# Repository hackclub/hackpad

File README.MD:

Talk to @Ace (Zohair shaik) on slack Gmail: Zohairshaik7@gmail.com Discord: autohackingcodes2079Hi this is my hackpad submission:

________________________________________________
Why I made it:

Was pretty bored and saw some macropads on insta so i got inspired..
________________________________________________
What I need:

7x Cherry MX switches
2x SK6812 MINI Leds
7x Blank DSA Keycaps
________________________________________________

______________________________________________
Firmware used:

KMK

_______________________________________________

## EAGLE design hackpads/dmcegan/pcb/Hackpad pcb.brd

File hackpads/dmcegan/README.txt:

BOM:
1x PCB
1x RP2040
11x Cherry Mx switches (Milky Yellow)
11x Keycaps

What was your inspiration to make it?:
My inspiration was the fact that I had been looking at macropads for a while but never actually got around to making one. I also needed something to control the controls in certain apps like discord, fusion 360 and prusaslicer without resorting to complicated shortcuts.
Hardest challenges faced:
FIRMWARE. The firmware was the most complicated part of the build by far as ive designed pcbs and 3d models before. The firmware is still a bit iffy as all the guides I could find required the rp2040 to actually compile the full .uf2 fgile, so hopefully this is something to work on once i've to the physical parts.
Other fun facts to know:
This is something i've wanted to do for a while and now I get do do it! I think hack club is a great thing for high schoolers as it gives the motivation and funds to experiment and have fun with cool projects like this, so thanks guys!

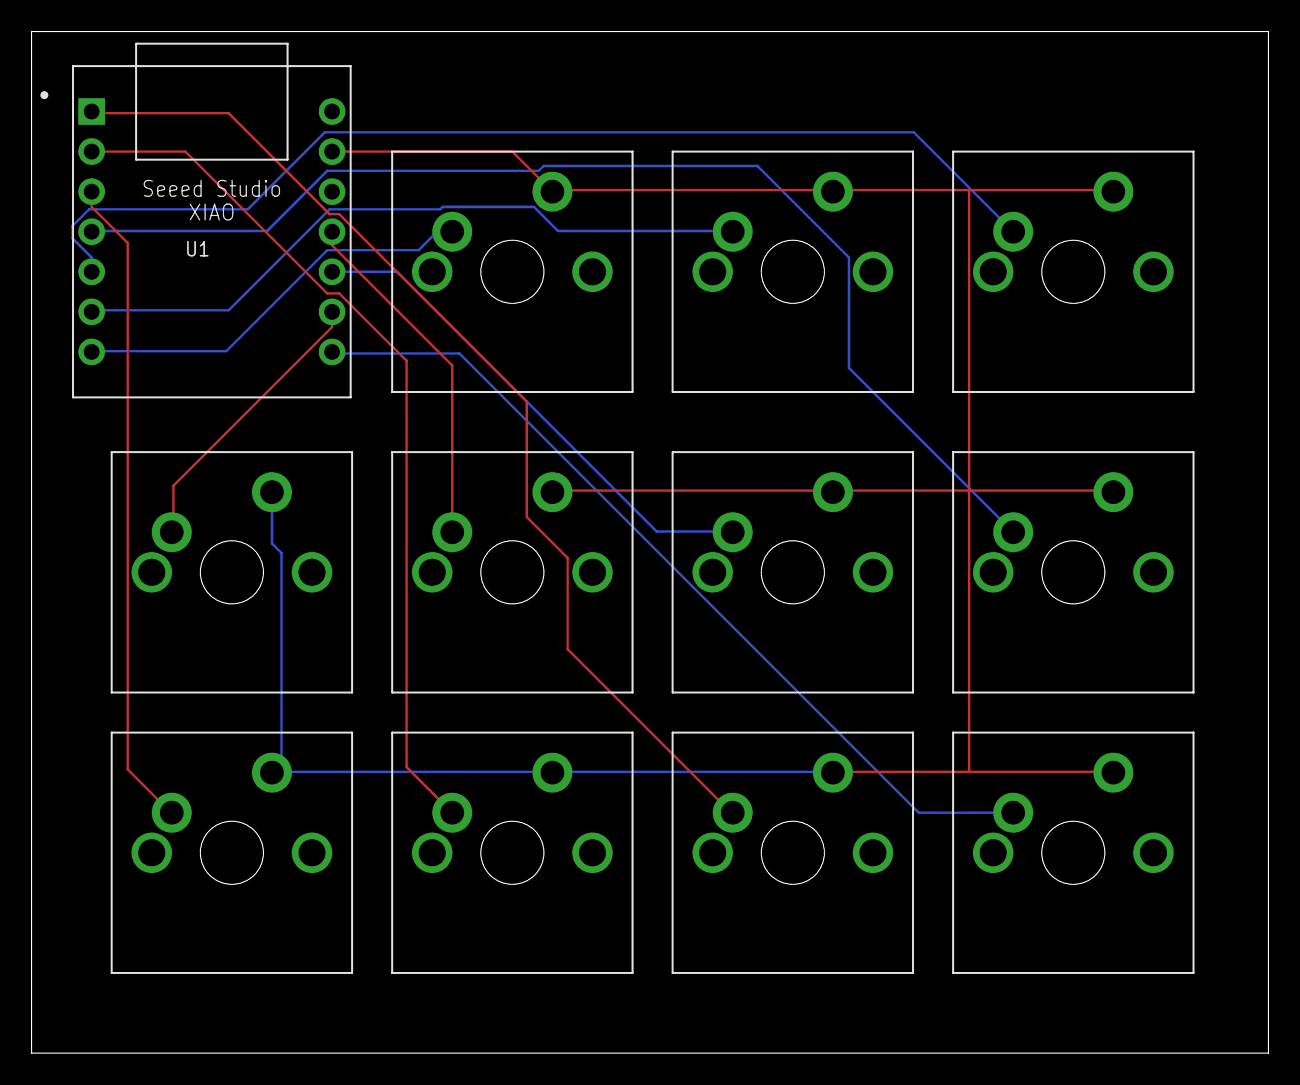
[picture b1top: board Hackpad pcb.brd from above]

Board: 2 copper layers, 78.4 x 64.8 mm, 12 parts (0 on the bottom side), 12 nets.

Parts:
U1: XIAO-THRUHOLE; XIAO-GENERIC-THRUHOLE-MODULE14P-2.54-21X17.8MM
U$1, U$2, U$3, U$4, U$5, U$6, U$7, U$8, U$9, U$10, U$11: CHERRY-MX

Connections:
GND: U1.13, U$1.SW2, U$2.SW2, U$3.SW2, U$4.SW2, U$5.SW2, U$6.SW2, U$7.SW2, U$8.SW2, U$9.SW2, U$10.SW2, U$11.SW2
unnamed: U1.1, U$5.SW1
unnamed: U1.2, U$6.SW1
unnamed: U1.3, U$7.SW1
unnamed: U1.4, U$8.SW1
unnamed: U1.5, U$9.SW1
unnamed: U1.6, U$10.SW1
unnamed: U1.7, U$11.SW1
unnamed: U1.11, U$1.SW1
unnamed: U1.10, U$2.SW1
unnamed: U1.9, U$3.SW1
unnamed: U1.8, U$4.SW1

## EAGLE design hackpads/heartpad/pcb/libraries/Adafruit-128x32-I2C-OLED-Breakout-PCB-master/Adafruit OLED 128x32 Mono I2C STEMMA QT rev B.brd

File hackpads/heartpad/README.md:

# Heartpad

## Firmware
**Things to Test:**

1. Please make sure that the display is working and is showing this image:
<!-- [oled display image](./Firmware/catswhite.bmp) -->

2. Please test the toggle key to toggle between layers

3. Please test the function keys on the first layer. You don't need to test the second layer, since I will use an application to create custom keybinds for those

## CAD 

- Please ensure that the case fits

## PCB

- It would be nice if you could double check my wiring on the PCB and schematic

## BOM

- 10x Cherry MX Switches

- 1x PCB - Color: Purple

- 1x 0.91" 128x32 I2C OLED Display

- 10x Through-hold 1N4148 Diodes

- Screws (18mm tall, 3mm diameter) with nuts

- 1x Case - Filament Color: Carmine Red Glitter Filament

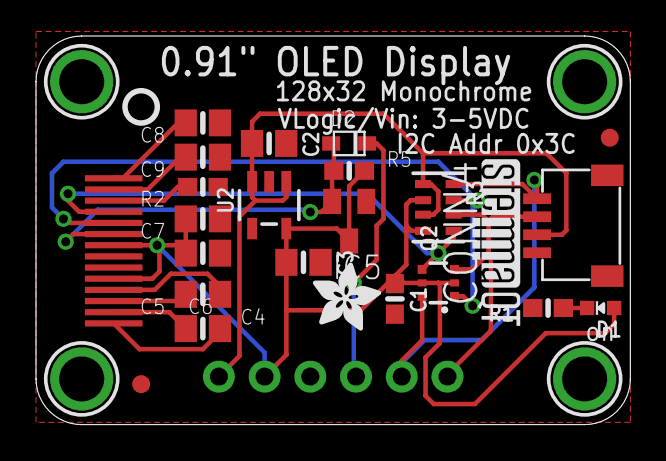
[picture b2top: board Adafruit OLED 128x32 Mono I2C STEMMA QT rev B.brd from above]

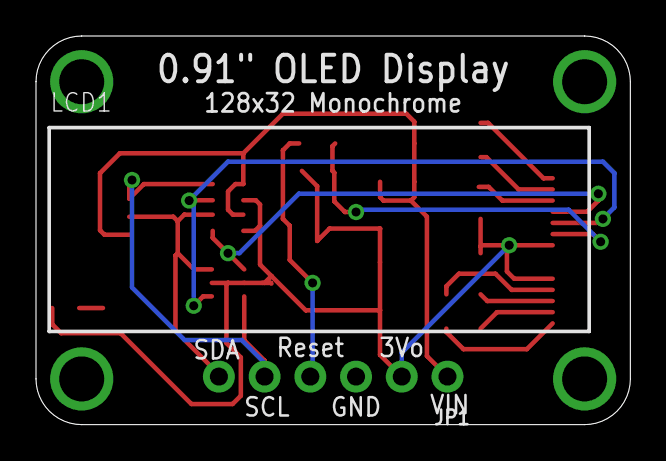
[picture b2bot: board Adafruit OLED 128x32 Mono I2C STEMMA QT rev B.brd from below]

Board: 2 copper layers, 33.0 x 21.6 mm, 30 parts (2 on the bottom side), 17 nets.

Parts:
C1: 0.1uF; 0603-NO
C2, C3, C8, C9: 10uF; 0805-NO
C4, C5, C6, C7: 1uF; 0805-NO
CONN4: STEMMA_I2C_QT; JST_SH4
D1: GREEN; CHIPLED_0603_NOOUTLINE
D2: 1N4148; SOD-323F
FID3, FID4: FIDUCIAL_1MM
IC5: APX803; SOT23
JP1: 1X06_ROUND_70
LCD1: UG-2832HSWEG02_WRAPUNDER
Q2: BSS138; SOT363
R1, R5: 10K; 0603-NO
R2: 390K; 0603-NO
R3: 10K; RESPACK_4X0603
U2: AP2112K-3.3; SOT23-5
U$1, U$17, U$19, U$21: MOUNTINGHOLE2.5; MOUNTINGHOLE_2.5_PLATED
U$22: ADAFRUIT_3.5MM
U$25: PCBFEAT-REV-040
U$31: STEMMAQT

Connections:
3.3V: C1.1, C3.1, C6.2, C7.2, D1.A, IC5.3, JP1.2, LCD1.5, LCD1.8, Q2.2, Q2.5, R3.2, R3.4, R5.2, U2.5
GND: C1.2, C2.2, C3.2, C6.1, C7.1, C8.1, C9.1, CONN4.1, IC5.1, JP1.3, LCD1.7, R1.2, R2.1, U2.2
unnamed: C4.2, LCD1.1
unnamed: D1.C, R1.1
unnamed: C4.1, LCD1.2
unnamed: C5.2, LCD1.3
unnamed: C5.1, LCD1.4
unnamed: C9.2, LCD1.13
unnamed: LCD1.12, R2.2
unnamed: C8.2, LCD1.14
RESET: D2.C, JP1.4
RES_3V: D2.A, IC5.2, LCD1.9, R5.1
SCL: CONN4.4, JP1.5, Q2.6, R3.8
SCL_3V: LCD1.10, Q2.1, R3.7
SDA: CONN4.3, JP1.6, Q2.3, R3.6
SDA_3V: LCD1.11, Q2.4, R3.5
VCC: C2.1, CONN4.2, JP1.1, R3.1, R3.3, U2.1, U2.3

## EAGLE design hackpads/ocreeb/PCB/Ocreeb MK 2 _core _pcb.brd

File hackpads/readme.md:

# madpad

* Keyboard Maintainer: [Meghana Madiraju](https://github.com/MeghanaM4)
* Hardware Supported: *The PCBs, controllers supported*
* Hardware Availability: *Links to where you can find this hardware*

Make example for this keyboard (after setting up your build environment):

    make madpad:default

Flashing example for this keyboard:

    make madpad:default:flash

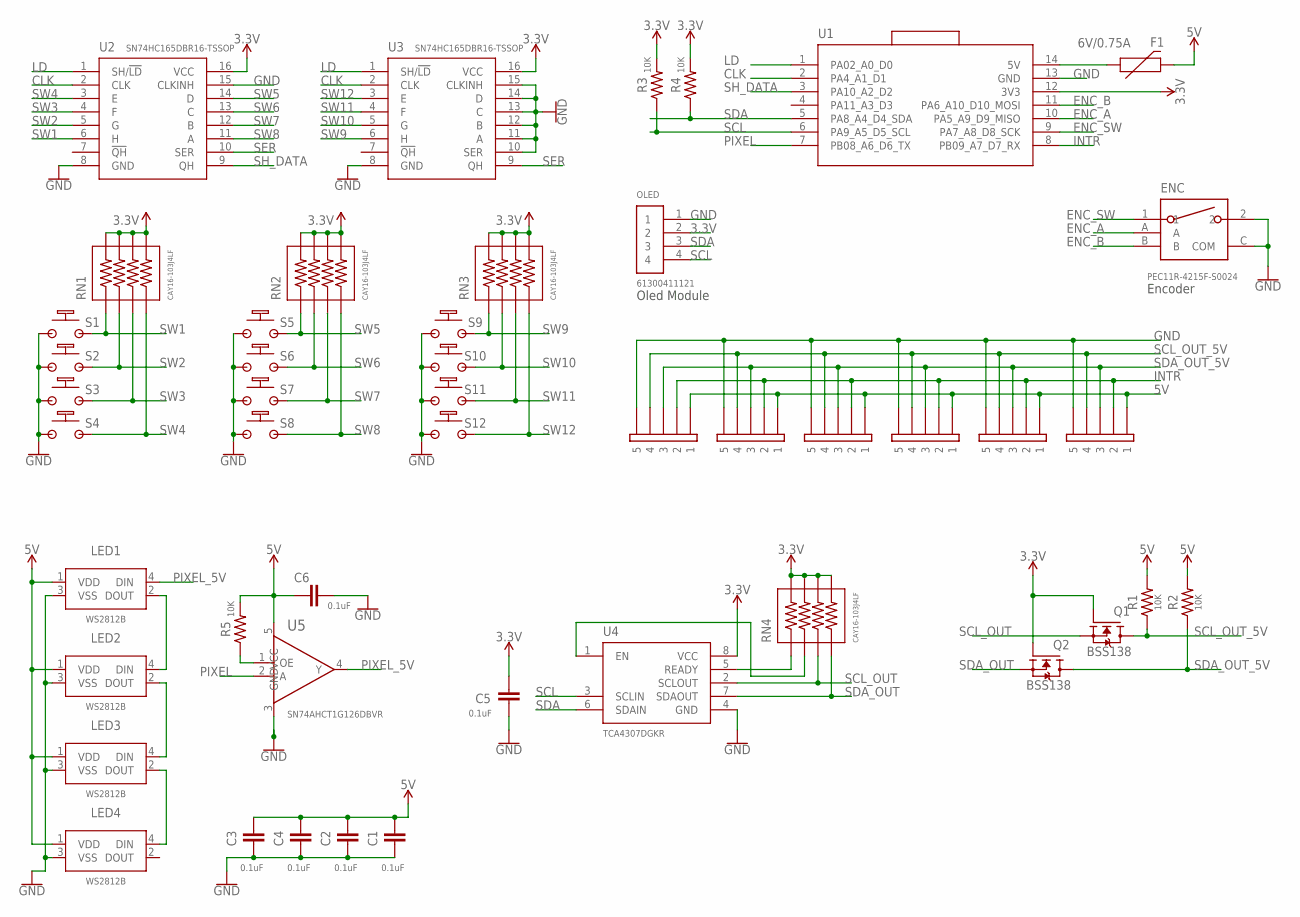
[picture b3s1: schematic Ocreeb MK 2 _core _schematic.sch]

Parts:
C1, C2, C3, C4, C5, C6: 0.1uF; CAPC1608X85
ENC: PEC11R-4215F-S0024
F1: 6V/0.75A; 1206
LED1, LED2, LED3, LED4: WS2812B
OLED: 61300411121
Q1, Q2: BSS138; SOT95P240X111-3N
R1, R2, R3, R4, R5: 10K; RESC1608X60
RN1, RN2, RN3, RN4: CAY16-103J4LF; RESCAF80P320X160X60-8N
S1, S2, S3, S4, S5, S6, S7, S8, S9, S10, S11, S12: MX1A-11NN; CHERRY_MX1A-11NN_SWITCH
U1: MOUDLE-SEEEDUINO-XIAO-SMD; MOUDLE14P-SMD-2.54-21X17.8MM
U2, U3: SN74HC165DBR16-TSSOP; SOP65P640X120-16N
U4: TCA4307DGKR; SOP65P490X110-8N
U5: SN74AHCT1G126DBVR; SOT95P280X145-5N
U$1, U$2, U$3, U$4, U$5, U$6: 5PIN_EDGE; 5_POGO_EDGE

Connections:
3.3V: C5.2, OLED.2, Q1.1 (G), Q2.1 (G), R3.2, R4.2, RN1.5, RN1.6, RN1.7, RN1.8, RN2.5, RN2.6, RN2.7, RN2.8, RN3.5, RN3.6, RN3.7, RN3.8, RN4.5, RN4.6, RN4.7, RN4.8, U1.12 (3V3), U2.16 (VCC), U3.16 (VCC), U4.8 (VCC)
5V: C1.2, C2.2, C3.2, C4.2, C6.2, F1.2, LED1.1 (VDD), LED2.1 (VDD), LED3.1 (VDD), LED4.1 (VDD), R1.2, R2.2, R5.2, U5.5 (VCC), U$1.1, U$2.1, U$3.1, U$4.1, U$5.1, U$6.1
CLK: U1.2 (PA4_A1_D1), U2.2 (CLK), U3.2 (CLK)
ENC_A: ENC.A, U1.10 (PA5_A9_D9_MISO)
ENC_B: ENC.B, U1.11 (PA6_A10_D10_MOSI)
ENC_SW: ENC.1, U1.9 (PA7_A8_D8_SCK)
GND: C1.1, C2.1, C3.1, C4.1, C5.1, C6.1, ENC.2, ENC.C (COM), LED1.3 (VSS), LED2.3 (VSS), LED3.3 (VSS), LED4.3 (VSS), OLED.1, S1.1, S1.1_ALT (1), S2.1, S2.1_ALT (1), S3.1, S3.1_ALT (1), S4.1, S4.1_ALT (1), S5.1, S5.1_ALT (1), S6.1, S6.1_ALT (1), S7.1, S7.1_ALT (1), S8.1, S8.1_ALT (1), S9.1, S9.1_ALT (1), S10.1, S10.1_ALT (1), S11.1, S11.1_ALT (1), S12.1, S12.1_ALT (1), U1.13 (GND), U2.8 (GND), U2.15 (CLKINH), U3.8 (GND), U3.10 (SER), U3.11 (A), U3.12 (B), U3.13 (C), U3.14 (D), U3.15 (CLKINH), U4.4 (GND), U5.3 (GND), U$1.5, U$2.5, U$3.5, U$4.5, U$5.5, U$6.5
INTR: U1.8 (PB09_A7_D7_RX), U$1.2, U$2.2, U$3.2, U$4.2, U$5.2, U$6.2
LD: U1.1 (PA02_A0_D0), U2.1 (SH/!LD), U3.1 (SH/!LD)
unnamed: RN4.1, U4.5 (READY)
unnamed: R5.1, U5.1 (OE)
unnamed: LED1.2 (DOUT), LED2.4 (DIN)
unnamed: LED2.2 (DOUT), LED3.4 (DIN)
unnamed: LED3.2 (DOUT), LED4.4 (DIN)
unnamed: RN4.2, U4.1 (EN)
PIXEL: U1.7 (PB08_A6_D6_TX), U5.2 (A)
PIXEL_5V: LED1.4 (DIN), U5.4 (Y)
SCL: OLED.4, R3.1, U1.6 (PA9_A5_D5_SCL), U4.3 (SCLIN)
SCL_OUT: Q1.2 (S), RN4.3, U4.2 (SCLOUT)
SCL_OUT_5V: Q1.3 (D), R1.1, U$1.4, U$2.4, U$3.4, U$4.4, U$5.4, U$6.4
SDA: OLED.3, R4.1, U1.5 (PA8_A4_D4_SDA), U4.6 (SDAIN)
SDA_OUT: Q2.2 (S), RN4.4, U4.7 (SDAOUT)
SDA_OUT_5V: Q2.3 (D), R2.1, U$1.3, U$2.3, U$3.3, U$4.3, U$5.3, U$6.3
SER: U2.10 (SER), U3.9 (QH)
SH_DATA: U1.3 (PA10_A2_D2), U2.9 (QH)
SW1: RN1.1, S1.2, S1.2_ALT (2), U2.6 (H)
SW2: RN1.2, S2.2, S2.2_ALT (2), U2.5 (G)
SW3: RN1.3, S3.2, S3.2_ALT (2), U2.4 (F)
SW4: RN1.4, S4.2, S4.2_ALT (2), U2.3 (E)
SW5: RN2.1, S5.2, S5.2_ALT (2), U2.14 (D)
SW6: RN2.2, S6.2, S6.2_ALT (2), U2.13 (C)
SW7: RN2.3, S7.2, S7.2_ALT (2), U2.12 (B)
SW8: RN2.4, S8.2, S8.2_ALT (2), U2.11 (A)
SW9: RN3.1, S9.2, S9.2_ALT (2), U3.6 (H)
SW10: RN3.2, S10.2, S10.2_ALT (2), U3.5 (G)
SW11: RN3.3, S11.2, S11.2_ALT (2), U3.4 (F)
SW12: RN3.4, S12.2, S12.2_ALT (2), U3.3 (E)
USB_5V: F1.1, U1.14 (5V)

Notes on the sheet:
Oled Module
Encoder

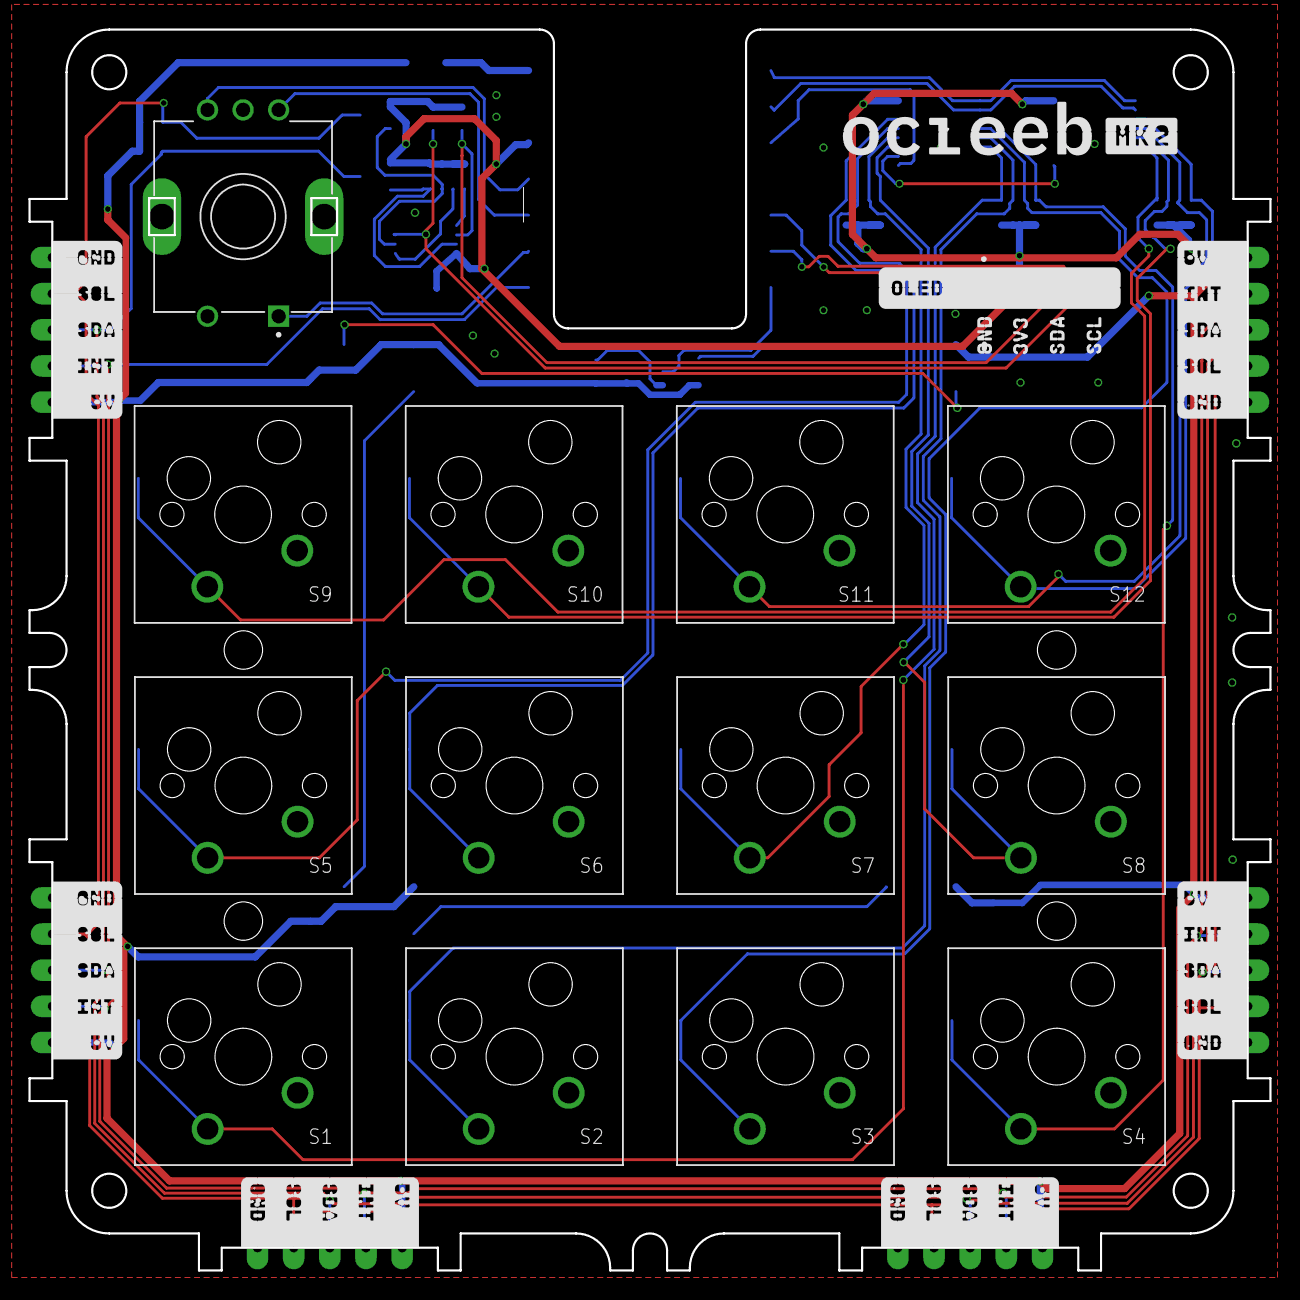
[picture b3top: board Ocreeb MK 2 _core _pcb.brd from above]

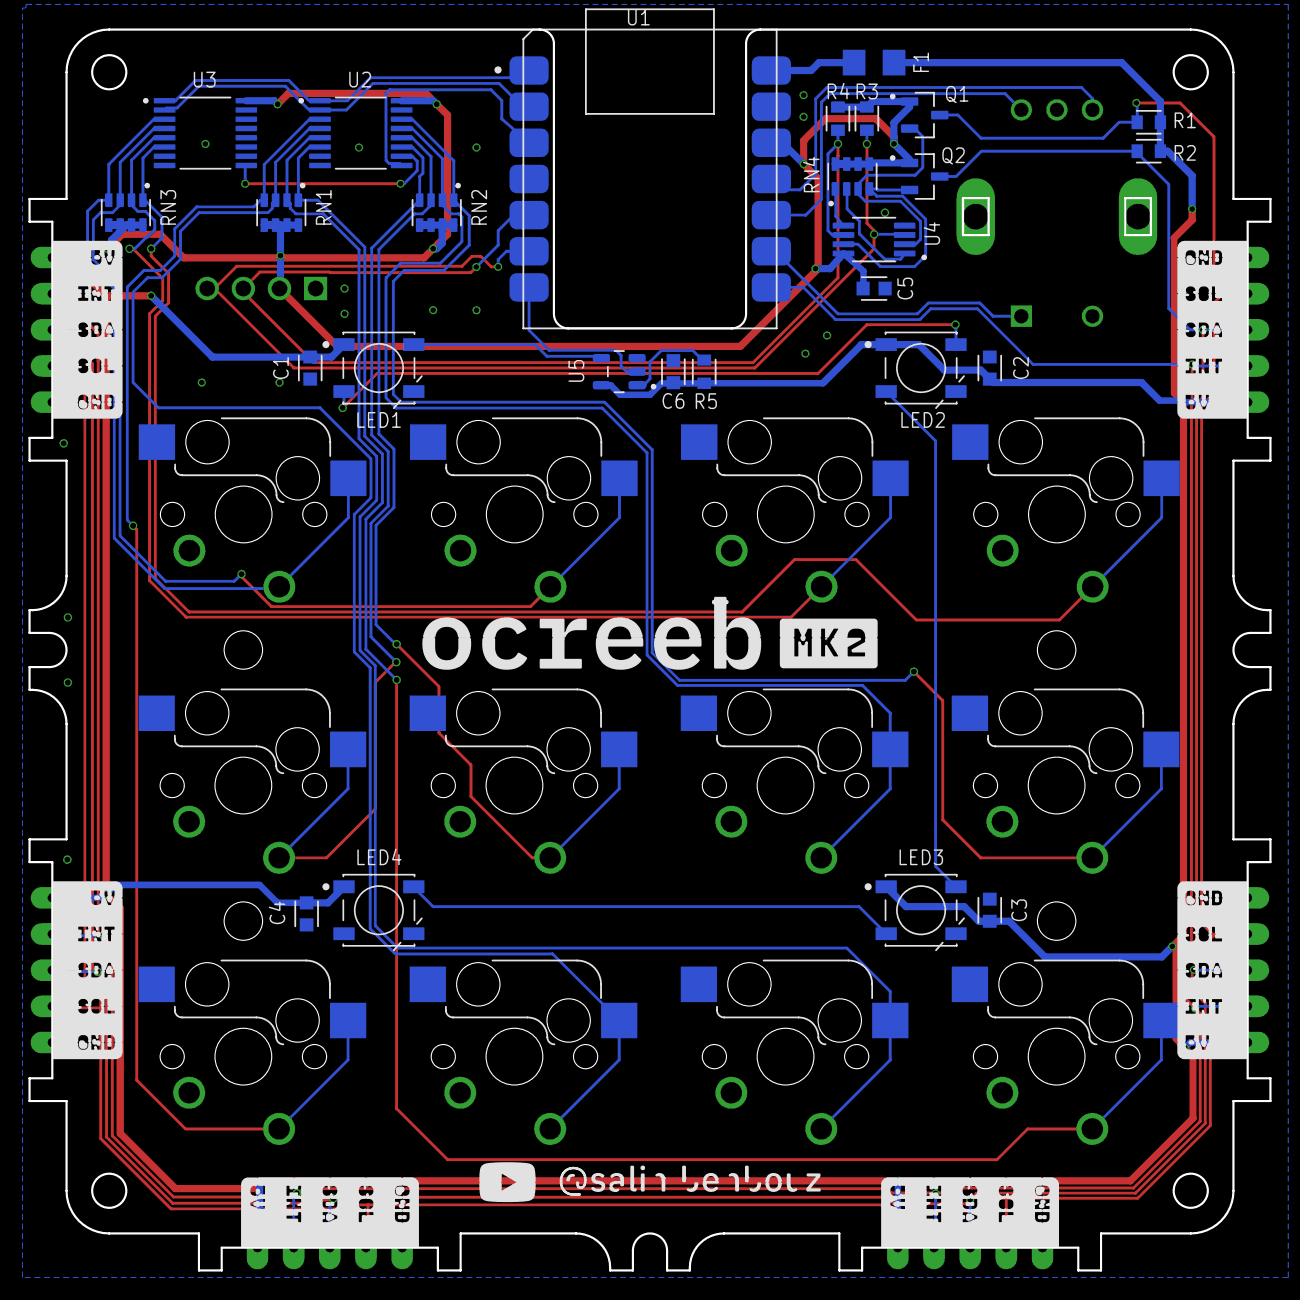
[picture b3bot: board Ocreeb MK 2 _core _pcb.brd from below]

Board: 2 copper layers, 87.2 x 87.2 mm, 47 parts (27 on the bottom side), 38 nets.

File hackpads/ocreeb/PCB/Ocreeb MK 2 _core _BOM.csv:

Qty,Parts,Device,Value,Package,MP,Digikey,Type,Description
1,U1,XIAO RP2040,,,102010428,1597-102010428-ND,SMD,RP2040 XIAO RP2040 - ARM® Cortex®-M0+ MCU 32-Bit
6,"C1, C2, C3, C4, C5, C6",C_CHIP-0603(1608-METRIC),0.1uF,CAPC1608X85,C0603C104M5RAC7867,399-C0603C104M5RAC7867CT-ND,SMD,0.1 µF ±20% 50V Ceramic Capacitor X7R 0603 (1608 Metric)
5,"R1, R2, R3, R4, R5",R-US_CHIP-0603(1608-METRIC),10K,RESC1608X60,RMCF0603FT10K0,RMCF0603FT10K0CT-ND,SMD,"10 kOhms ±1% 0.1W, 1/10W Chip Resistor 0603 (1608 Metric)"
1,F1,PPTC_0.75A,6V/0.75A,1206 (3216 Metric),PTS12066V075,283-PTS12066V075CT-ND,SMD,"Polymeric PTC Resettable Fuse 6V 750 mA Ih Surface Mount 1206 (3216 Metric), Concave"
2,"Q1, Q2",BSS138,BSS138,SOT-23-3,BSS138,4530-BSS138CT-ND,SMD,N-Channel 50 V 220mA (Ta) 350mW (Ta) Surface Mount SOT-23
4,"RN1, RN2, RN3, RN4",CAY16-103J4LF,CAY16-103J4LF,1206 (3216 Metric),CAY16-103J4LF,CAY16-103J4LFCT-ND,SMD,"10k Ohm ±5% 62.5mW Power Per Element Isolated 4 Resistor Network/Array ±200ppm/°C 1206 (3216 Metric), Convex, Long Side Terminals"
1,U5,SN74AHCT1G126DBVR,SN74AHCT1G126DBVR,SOT-23-5,SN74AHCT1G126DBVR,296-4710-1-ND,SMD,"Buffer, Non-Inverting 1 Element 1 Bit per Element 3-State Output SOT-23-5"
2,"U2, U3",SN74HC165DBR16-TSSOP,SN74HC165DBR16-TSSOP,16-SSOP,SN74HC165DBR,296-23151-1-ND,SMD,Shift Shift Register 1 Element 8 Bit 16-SSOP
1,U4,TCA4307DGKR,TCA4307DGKR,8-VSSOP,TCA4307DGKR,296-TCA4307DGKRCT-ND,SMD,Hot Swap Controller 1 Channel General Purpose 8-VSSOP
4,"LED1, LED2, LED3, LED4",WS2812B,WS2812B,WS2812B,COM-16347,1568-COM-16347CT-ND,SMD,"Addressable Lighting - LED Serial NRZ (Shift Register) Red, Green, Blue (RGB)"
1,ENC,PEC11R-4215F-S0024,PEC11R-4215F-S0024,PEC11R-4215F-S0024,PEC11R-4215F-S0024,PEC11R-4215F-S0024-ND,TH,Rotary Encoder Mechanical 24 Quadrature (Incremental) Vertical
12,"S1, S2, S3, S4, S5, S6, S7, S8, S9, S10, S11, S12",MX HOT SWAP SOCKETS,,20 Pack,4958,1528-4958-ND,SMD,Kailh MX Hotswap Sockets
12,"S1, S2, S3, S4, S5, S6, S7, S8, S9, S10, S11, S12",MX SWITCHES,,12 Pack,5122,1528-5122-ND,TH,MX-Compatible Mechanical Keys
1,OLED,OLED MODULE,,3 pcs,,,MOD,0.91 inch OLED Display Module SSD1306 I2C 128x32
6,CONNECTOR,5PIN_EDGE_LANDING,,5 pcs,,,SUB,Custom landing pads PCB
4,SCR,M2 x 6mm,,Assorted Lengths Kit,,,SCR,M2 Self-Tapping Screws
3,SCR,M2 x 12mm,,Assorted Lengths Kit,,,SCR,M2 Self-Tapping Screws
4,SCR,M2 x 16mm,,Assorted Lengths Kit,,,SCR,M2 Self-Tapping Screws
12,MAG,6 x 3mm,,40 pcs,,,MAG,Small Neodymium Magnets
4,ADH,6 x 2 mm,,Assorted Kit,,,ADH,Adhesive Bumper Pads Self Stick

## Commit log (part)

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2025-03-20 Add Branding to all parts
2025-03-20 update deltaboard
2025-03-21 Krishveer's Hackboard
2025-03-21 remove OLED library
2025-03-21 remove OPL lib
2025-03-21 remove models (1)
2025-03-21 remove models (2)
2025-03-22 Uploaded Hyperboard files
2025-03-22 feat: Add virtual_keyboard
    @virtualfuzz keyboard
2025-03-22 feat: Add link to the original repo
2025-03-22 Added GamerBoard
2025-03-22 added cardgrant page
2025-03-22 revised docs
2025-03-22 updated hackboard
2025-03-22 fixed main.tsx by removign unused imports
2025-03-22 Add OLED cutout
2025-03-22 add oled slit
2025-03-22 update screenshot
2025-03-22 fix the tiny problem in the readme
2025-03-23 Add files via upload
    add text branding on bottom of both cases
2025-03-23 fixed all issues please approve
2025-03-23 remove submodule
2025-03-23 sync submodule
2025-03-23 fix bold text
2025-03-23 add myCompactKeyboard
2025-03-23 add silk screen text for myCompactKeyboard
2025-03-23 Finalise Case (Fix screw and insert issues)
2025-03-24 Pending changes exported from your codespace
2025-03-25 Update midipad with revised version
2025-03-25 Update README.md for midipad
2025-03-26 Adding Barni Keyboard
2025-03-27 BOM update
2025-03-27 Fix accidental deletion
2025-03-29 Fixed tolerances
2025-03-29 Final README.md
2025-03-30 fix: add case opening for usb
2025-03-30 Connect sda/scl for robopad
2025-04-04 fixed bottom shell to print without support
2025-04-05 Updated CAD
2025-04-08 fix: move basmati.step to CAD/
2025-04-09 Revamped Hackpad README, removed unnecessary libraries
2025-04-11 Remodel case in Fusion 360
2025-04-12 Remove libraries from robopad
2025-04-12 fix reame
2025-04-12 endboard
2025-04-14 add ninefold
2025-04-14 Rename macropad.zip to gerber.zip
2025-04-14 Revert "endboard"
    This reverts commit ae698ac5931ae4c96808389b3cca61e4a54952d2.
2025-04-14 Removed extra files
2025-04-20 update deltaboard (fix bugs)
2025-05-01 added kicad pro files
2025-05-02 Add images
2025-05-02 add case images
2025-05-02 remove broken pics
2025-05-03 Add new versions
2025-05-04 Delete hackpads/HexadeciPad/pcb/OPL_Kicad_Library-master directory
    Delete pcb libraries
2025-05-13 Add ghostpad
2025-05-14 edited reqs
2025-05-18 made README.md
2025-05-18 forgot schematic screenshot, so uploaded it
2025-05-20 Add LazyPad hackpad
2025-05-20 add cad zip (step was too big)
2025-05-21 uploaded pcb files
2025-05-21 added gerbers
2025-05-22 updated docs for v3
2025-05-24 Fix broken link in submission page
2025-05-29 updated docs
2025-05-30 reduced the size of the files of pinuspad
2025-06-04 updated site. should be good for v3
2025-06-06 morseboard added this time, no weird git stuff
2025-06-06 readme change, talks more about the inspiration.
2025-06-06 Added BOM.csv
2025-06-08 Correct and improve BOM
2025-06-08 Update and improve BOM
2025-06-10 Add drill files to gerbers.zip
2025-06-11 added new knob file
2025-06-11 moved misplaced hackpad
2025-06-26 Add my hackpad
2025-06-27 Add NormalPad
2025-06-27 Overwrite with new designs
2025-06-27 Fixed?? The images
2025-06-29 Override crappy files with good ones HOPEFULLY LAST TIME
2025-06-29 Fixed images?
2025-07-17 Create CAD
2025-07-17 Add CAD Files
2025-07-17 Create PCB
2025-10-05 Fix formatting of checklist items in Overview.mdx
2025-10-05 Enhance Overview with README and project visuals
    Added sections for README content and project pictures.
2025-10-06 Delete hackpads/ChessPad/PCB/ChessPad_KiCad_Folder/Seeed Studio XIAO Series Library directory
    I was asked to when someone reviewed it, that's all.
2025-10-06 Create file1
2025-10-06 added production stuff
2025-10-11 fixed a typo that pointed beginners to #highway not #blueprint
    As highway is closed, the link now redirects to the blueprint homepage
2025-10-12 added as normal
2025-10-13 refactor(woagpad): replace git submodule with raw src
2025-10-13 refactor(woagpad): replace git submodule with raw src take 2
2025-10-14 removed backups
2025-10-14 Remove libraries
2025-10-15 removed unnecessary files
2025-10-17 fix: spelling
2025-10-18 Enhance README with description and images
    Updated README with a description and new image links.
2025-10-18 I shouldn't have been keeping v1 files
2025-10-18 update firepad files (I thought I did this ages ago oops :/)
2025-10-18 Update README slightly
2025-12-20 Fix expired xdn link
2026-01-23 Fix typo in Tutorial.mdx regarding rectangle placement
2026-02-17 update: clarify formats
2026-03-22 Add WizPad submission by wizrizz
2026-03-22 Add 3D printable case STL
2026-03-22 Fix 100mm rule compliance and high-quality render
2026-03-22 Update to WizPad Ultra Case - Ergonomic High Profile Design
2026-03-22 ULTIMATE UPGRADE: Added OLED Display, Keycaps, and high-detail render
2026-03-25 Fix SK6812MINI-E footprint to stop the model from breaking
2026-04-01 edit spelling
2026-04-04 Fix code block formatting in SimpleTutorial.mdx
    Updated code block formatting for clarity in tutorial.
    In current web site, the last comma isn't appeared:
    ["","",""]
    ↑It should be : ["","",""],
    Because without the last comma, plate generator couldn't work well.
2026-04-09 Bump vite from 5.4.3 to 6.4.2 in /website
    Bumps [vite](https://github.com/vitejs/vite/tree/HEAD/packages/vite) from 5.4.3 to 6.4.2.
    - [Release notes](https://github.com/vitejs/vite/releases)
    - [Changelog](https://github.com/vitejs/vite/blob/v6.4.2/packages/vite/CHANGELOG.md)
    - [Commits](https://github.com/vitejs/vite/commits/v6.4.2/packages/vite)
    ---
    updated-dependencies:
2026-04-24 Bump postcss from 8.4.45 to 8.5.10 in /website
    Bumps [postcss](https://github.com/postcss/postcss) from 8.4.45 to 8.5.10.
    - [Release notes](https://github.com/postcss/postcss/releases)
    - [Changelog](https://github.com/postcss/postcss/blob/main/CHANGELOG.md)
    - [Commits](https://github.com/postcss/postcss/compare/8.4.45...8.5.10)
    ---
    updated-dependencies:
2026-06-04 Add Hexpad macropad submission
2026-06-05 add 404 not found page and wired it into the router as a global catch-all route so unknown paths now show a matching hackpad-style 404 page
2026-06-25 Add LG Hackpad submission
    9-key macropad (XIAO RP2040) with rotary encoder profile-browser and
    OLED, custom PCB (68 x 99.68 mm, 2-layer, DRC clean), no-supports
    3D-printed open case, CircuitPython firmware. First-ever PCB.

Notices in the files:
parts and their libraries:
microbuilder: This work is placed in the public domain, and may be freely used for commercial and non-commercial work with the following conditions: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
SparkFun-Fuses: Licensing: Creative Commons ShareAlike 4.0 International - https://creativecommons.org/licenses/by-sa/4.0
